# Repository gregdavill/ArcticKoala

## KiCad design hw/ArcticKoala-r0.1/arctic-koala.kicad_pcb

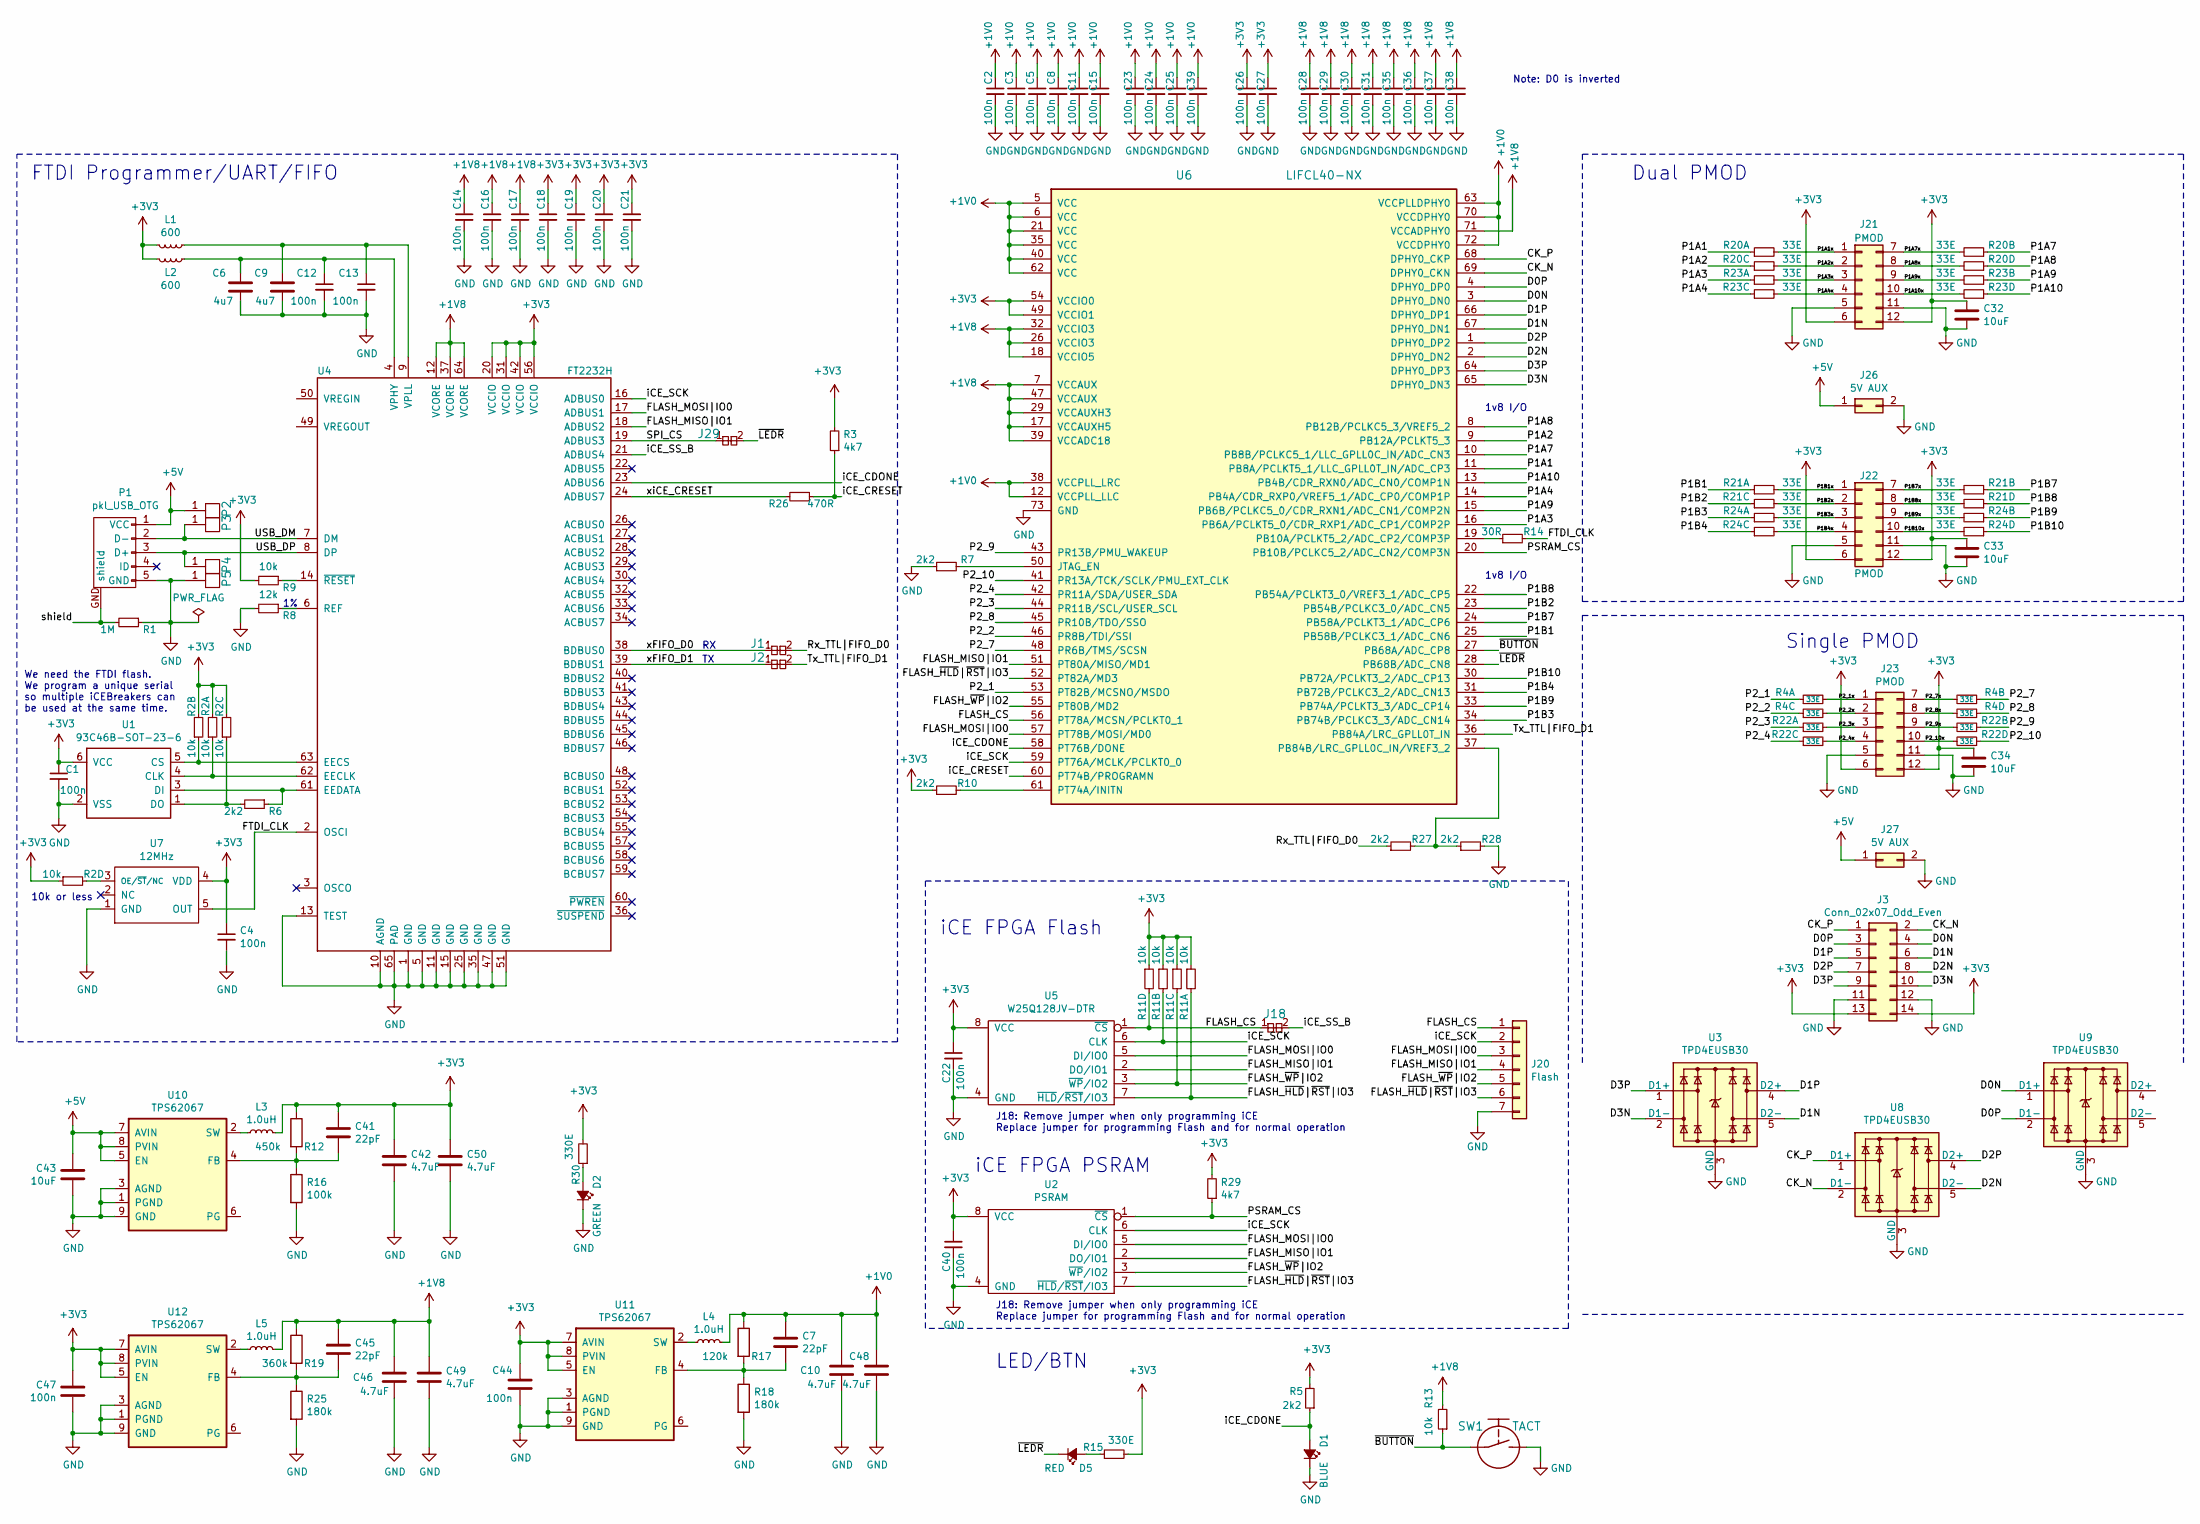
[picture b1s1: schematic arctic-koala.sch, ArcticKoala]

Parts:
C1, C2, C3, C4, C5, C8, C11, C12, C13, C14, C15, C16, C17, C18, C19, C20, C21, C22, C23, C24, C25, C26, C27, C28, C29, C30, C31, C35, C36, C37, C38, C39, C40, C44, C47: 100n; C_0402
C6, C9: 4u7; C_0603
C7, C41, C45: 22pF; C_0402
C10, C42, C46, C48, C49, C50: 4.7uF; C_0402
C32, C33, C34, C43: 10uF; C_0603
D1: BLUE; D_0603
D2: GREEN; D_0603
D5: RED; D_0603
J1, J2, J18, J29: Jumper; J_NC_0603_15
J3: Conn_02x07_Odd_Even; PinSocket_2x07_P2.54mm_Vertical
J20: Flash; Pin_Header_Straight_1x07
J21, J22, J23: PMOD; Socket_Strip_Angled_2x06
J26, J27: 5V AUX; Pin_Header_Straight_2x01
L1, L2: 600; L_0402
L3, L4, L5: 1.0uH; L_0603_1608Metric
P1: pkl_USB_OTG; Connector_USB_Micro_B_SMD
P2, P3, P4, P5: UP; PAD_SMD_1x2.65
R1: 1M; R_0402
R2, R11: 10k; R_Array_Convex_4x0402
R3, R29: 4k7; R_0402
R4, R20, R21, R22, R23, R24: 33E; R_Array_Convex_4x0402
R5, R6, R7, R10, R27, R28: 2k2; R_0402
R8: 12k; R_0402
R9, R13: 10k; R_0402
R12: 450k; R_0402
R14: 30R; R_0402
R15, R30: 330E; R_0402
R16: 100k; R_0402
R17: 120k; R_0402
R18, R25: 180k; R_0402
R19: 360k; R_0402
R26: 470R; R_0402
SW1: TACT; SW_SPST_3x4x2.5
U1: 93C46B-SOT-23-6; SOT-23-6
U2: PSRAM; SOIC-8_5.3x5.3mm_Pitch1.27mm
U3, U8, U9: TPD4EUSB30; USON-10_2.5x1.0mm_P0.5mm
U4: FT2232H; QFN-64-4.45mm1EP_9x9mm_Pitch0.5mm
U5: W25Q128JV-DTR; SOIC-8_5.3x5.3mm_Pitch1.27mm
U6: LIFCL40-NX; QFN-72-1EP_10x10mm_P0.5mm_EP6x6mm
U7: 12MHz; SOT-23-5
U10, U11, U12: TPS62067; WSON-8-1EP_2x2mm_P0.5mm_EP0.9x1.6mm_ThermalVias

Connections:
+1V0: C2.1, C3.1, C5.1, C7.1, C8.1, C10.1, C11.1, C15.1, C23.1, C24.1, C25.1, C39.1, C48.1, L4.2, R17.1, U6.5 (VCC), U6.6 (VCC), U6.12 (VCCPLL_LLC), U6.21 (VCC), U6.35 (VCC), U6.38 (VCCPLL_LRC), U6.40 (VCC), U6.62 (VCC), U6.63 (VCCPLLDPHY0), U6.70 (VCCDPHY0), U6.72 (VCCDPHY0)
+1V8: C14.1, C16.1, C17.1, C28.1, C29.1, C30.1, C31.1, C35.1, C36.1, C37.1, C38.1, C45.1, C46.1, C49.1, L5.2, R13.2, R19.1, U4.12 (VCORE), U4.37 (VCORE), U4.64 (VCORE), U6.7 (VCCAUX), U6.17 (VCCAUXH5), U6.18 (VCCIO5), U6.26 (VCCIO3), U6.29 (VCCAUXH3), U6.32 (VCCIO3), U6.39 (VCCADC18), U6.47 (VCCAUX), U6.71 (VCCADPHY0)
+3V3: C1.1, C4.1, C18.1, C19.1, C20.1, C21.1, C22.1, C26.1, C27.1, C32.2, C33.2, C34.2, C40.1, C41.1, C42.1, C44.1, C47.1, C50.1, J3.13, J3.14, J21.6, J21.12, J22.6, J22.12, J23.6, J23.12, L1.1, L2.1, L3.2, R2.2, R2.4, R2.6, R2.7, R3.2, R5.2, R9.2, R10.1, R11.1, R11.3, R11.5, R11.7, R12.1, R15.2, R29.2, R30.2, U1.6 (VCC), U2.8 (VCC), U4.20 (VCCIO), U4.31 (VCCIO), U4.42 (VCCIO), U4.56 (VCCIO), U5.8 (VCC), U6.49 (VCCIO1), U6.54 (VCCIO0), U7.4 (VDD), U11.5 (EN), U11.7 (AVIN), U11.8 (PVIN), U12.5 (EN), U12.7 (AVIN), U12.8 (PVIN)
+5V: C43.1, J26.1, J27.1, P1.1 (VCC), P2.1, U10.5 (EN), U10.7 (AVIN), U10.8 (PVIN)
/CK_N: J3.2, U6.69 (DPHY0_CKN), U8.2 (D1-)
/CK_P: J3.1, U6.68 (DPHY0_CKP), U8.1 (D1+)
/D0N: J3.4, U6.3 (DPHY0_DN0), U9.1 (D1+)
/D0P: J3.3, U6.4 (DPHY0_DP0), U9.2 (D1-)
/D1N: J3.6, U3.5 (D2-), U6.67 (DPHY0_DN1)
/D1P: J3.5, U3.4 (D2+), U6.66 (DPHY0_DP1)
/D2N: J3.8, U6.2 (DPHY0_DN2), U8.5 (D2-)
/D2P: J3.7, U6.1 (DPHY0_DP2), U8.4 (D2+)
/D3N: J3.10, U3.2 (D1-), U6.65 (DPHY0_DN3)
/D3P: J3.9, U3.1 (D1+), U6.64 (DPHY0_DP3)
/FLASH_CS: J18.1, J20.1, R11.8, U5.1 (~CS), U6.56 (PT78A/MCSN/PCLKT0_1)
/FLASH_MISO|IO1: J20.4, U2.2 (DO/IO1), U4.18 (ADBUS2), U5.2 (DO/IO1), U6.51 (PT80A/MISO/MD1)
/FLASH_MOSI|IO0: J20.3, U2.5 (DI/IO0), U4.17 (ADBUS1), U5.5 (DI/IO0), U6.57 (PT78B/MOSI/MD0)
/FLASH_~HLD~|~RST~|IO3: J20.6, R11.2, U2.7 (~HLD~/~RST~/IO3), U5.7 (~HLD~/~RST~/IO3), U6.52 (PT82A/MD3)
/FLASH_~WP~|IO2: J20.5, R11.6, U2.3 (~WP~/IO2), U5.3 (~WP~/IO2), U6.55 (PT80B/MD2)
/FTDI_CLK: R14.2, U4.2 (OSCI), U7.5 (OUT)
/P1A1: R20.1, U6.11 (PB8A/PCLKT5_1/LLC_GPLL0T_IN/ADC_CP3)
/P1A1x: J21.1, R20.2
/P1A2: R20.5, U6.9 (PB12A/PCLKT5_3)
/P1A2x: J21.2, R20.6
/P1A3: R23.1, U6.16 (PB6A/PCLKT5_0/CDR_RXP1/ADC_CP1/COMP2P)
/P1A3x: J21.3, R23.2
/P1A4: R23.5, U6.14 (PB4A/CDR_RXP0/VREF5_1/ADC_CP0/COMP1P)
/P1A4x: J21.4, R23.6
/P1A7: R20.3, U6.10 (PB8B/PCLKC5_1/LLC_GPLL0C_IN/ADC_CN3)
/P1A7x: J21.7, R20.4
/P1A8: R20.7, U6.8 (PB12B/PCLKC5_3/VREF5_2)
/P1A8x: J21.8, R20.8
/P1A9: R23.3, U6.15 (PB6B/PCLKC5_0/CDR_RXN1/ADC_CN1/COMP2N)
/P1A9x: J21.9, R23.4
/P1A10: R23.7, U6.13 (PB4B/CDR_RXN0/ADC_CN0/COMP1N)
/P1A10x: J21.10, R23.8
/P1B1: R21.1, U6.25 (PB58B/PCLKC3_1/ADC_CN6)
/P1B1x: J22.1, R21.2
/P1B2: R21.5, U6.23 (PB54B/PCLKC3_0/ADC_CN5)
/P1B2x: J22.2, R21.6
/P1B3: R24.1, U6.34 (PB74B/PCLKC3_3/ADC_CN14)
/P1B3x: J22.3, R24.2
/P1B4: R24.5, U6.31 (PB72B/PCLKC3_2/ADC_CN13)
/P1B4x: J22.4, R24.6
/P1B7: R21.3, U6.24 (PB58A/PCLKT3_1/ADC_CP6)
/P1B7x: J22.7, R21.4
/P1B8: R21.7, U6.22 (PB54A/PCLKT3_0/VREF3_1/ADC_CP5)
/P1B8x: J22.8, R21.8
/P1B9: R24.3, U6.33 (PB74A/PCLKT3_3/ADC_CP14)
/P1B9x: J22.9, R24.4
/P1B10: R24.7, U6.30 (PB72A/PCLKT3_2/ADC_CP13)
/P1B10x: J22.10, R24.8
/P2_1: R4.1, U6.53 (PT82B/MCSNO/MSDO)
/P2_1x: J23.1, R4.2
/P2_2: R4.5, U6.46 (PR8B/TDI/SSI)
/P2_2x: J23.2, R4.6
/P2_3: R22.1, U6.44 (PR11B/SCL/USER_SCL)
/P2_3x: J23.3, R22.2
/P2_4: R22.5, U6.42 (PR11A/SDA/USER_SDA)
/P2_4x: J23.4, R22.6
/P2_7: R4.3, U6.48 (PR6B/TMS/SCSN)
/P2_7x: J23.7, R4.4
/P2_8: R4.7, U6.45 (PR10B/TDO/SSO)
/P2_8x: J23.8, R4.8
/P2_9: R22.3, U6.43 (PR13B/PMU_WAKEUP)
/P2_9x: J23.9, R22.4
/P2_10: R22.7, U6.41 (PR13A/TCK/SCLK/PMU_EXT_CLK)
/P2_10x: J23.10, R22.8
/PSRAM_CS: R29.1, U2.1 (~CS), U6.20 (PB10B/PCLKC5_2/ADC_CN2/COMP3N)
/Rx_TTL|FIFO_D0: J1.2, R27.1
/SPI_CS: J29.1, U4.19 (ADBUS3)
/Tx_TTL|FIFO_D1: J2.2, U6.36 (PB84A/LRC_GPLL0T_IN)
/USB_DM: P1.2 (D-), P3.1, U4.7 (DM)
/USB_DP: P1.3 (D+), P4.1, U4.8 (DP)
/iCE_CDONE: D1.A, R5.1, U4.23 (ADBUS6), U6.58 (PT76B/DONE)
/iCE_CRESET: R3.1, R26.1, U6.60 (PT74B/PROGRAMN); also elsewhere on the board
/iCE_SCK: J20.2, R11.4, U2.6 (CLK), U4.16 (ADBUS0), U5.6 (CLK), U6.59 (PT76A/MCLK/PCLKT0_0)
/iCE_SS_B: J18.2, U4.21 (ADBUS4)
/shield: P1.GND (shield), R1.2
/xFIFO_D0: J1.1, U4.38 (BDBUS0)
/xFIFO_D1: J2.1, U4.39 (BDBUS1)
/xiCE_CRESET: R26.2, U4.24 (ADBUS7)
/~BUTTON: R13.1, SW1.1, U6.27 (PB68A/ADC_CP8)
/~LEDR: D5.C, J29.2, U6.28 (PB68B/ADC_CN8)
GND: C1.2, C2.2, C3.2, C4.2, C5.2, C6.2, C8.2, C9.2, C10.2, C11.2, C12.2, C13.2, C14.2, C15.2, C16.2, C17.2, C18.2, C19.2, C20.2, C21.2, C22.2, C23.2, C24.2, C25.2, C26.2, C27.2, C28.2, C29.2, C30.2, C31.2, C32.1, C33.1, C34.1, C35.2, C36.2, C37.2, C38.2, C39.2, C40.2, C42.2, C43.2, C44.2, C46.2, C47.2, C48.2, C49.2, C50.2, D1.C, D2.C, J3.11, J3.12, J20.7, J21.5, J21.11, J22.5, J22.11, J23.5, J23.11, J26.2, J27.2, P1.5 (GND), P5.1, R1.1, R7.1, R8.2, R16.2, R18.2, R25.2, R28.2, SW1.2, U1.2 (VSS), U2.4 (GND), U3.3 (GND), U3.8 (GND), U4.1 (GND), U4.5 (GND), U4.10 (AGND), U4.11 (GND), U4.13 (TEST), U4.15 (GND), U4.25 (GND), U4.35 (GND), U4.47 (GND), U4.51 (GND), U4.65 (PAD), U5.4 (GND), U6.73 (GND), U7.1 (GND), U8.3 (GND), U8.8 (GND), U9.3 (GND), U9.8 (GND), U10.1 (PGND), U10.3 (AGND), U10.9 (GND), U11.1 (PGND), U11.3 (AGND), U11.9 (GND), U12.1 (PGND), U12.3 (AGND), U12.9 (GND); also elsewhere on the board
unnamed: C7.2, R17.2, R18.1, U11.4 (FB)
unnamed: C6.1, C12.1, L2.2, U4.4 (VPHY)
unnamed: C9.1, C13.1, L1.2, U4.9 (VPLL)
unnamed: C41.2, R12.2, R16.1, U10.4 (FB)
unnamed: C45.2, R19.2, R25.1, U12.4 (FB)
unnamed: D2.A, R30.1
unnamed: D5.A, R15.1
unnamed: L3.1, U10.2 (SW)
unnamed: L4.1, U11.2 (SW)
unnamed: L5.1, U12.2 (SW)
unnamed: R2.1, U1.4 (CLK), U4.62 (EECLK)
unnamed: R2.3, U1.5 (CS), U4.63 (EECS)
unnamed: R2.5, R6.2, U1.1 (DO)
unnamed: R2.8, U7.3 (OE/~ST~/NC)
unnamed: R6.1, U1.3 (DI), U4.61 (EEDATA)
unnamed: R7.2, U6.50 (JTAG_EN)
unnamed: R8.1, U4.6 (REF)
unnamed: R9.1, U4.14 (~RESET)
unnamed: R10.2, U6.61 (PT74A/INITN)
unnamed: R14.1, U6.19 (PB10A/PCLKT5_2/ADC_CP2/COMP3P)
unnamed: R27.2, R28.1, U6.37 (PB84B/LRC_GPLL0C_IN/VREF3_2)

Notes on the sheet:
10k or less
FTDI Programmer/UART/FIFO
J18: Remove jumper when only programming iCE Replace jumper for programming Flash and for normal operation
iCE FPGA Flash
Dual PMOD
Single PMOD
LED/BTN
We need the FTDI flash. We program a unique serial so multiple iCEBreakers can be used at the same time.
1v8 I/O
Note: D0 is inverted
iCE FPGA PSRAM

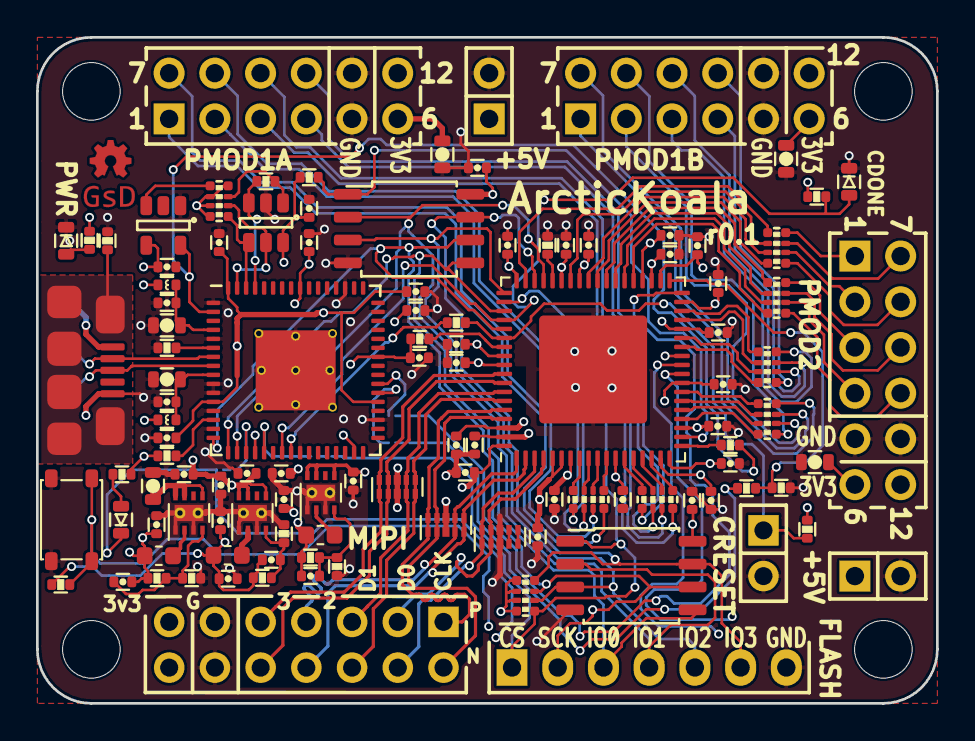
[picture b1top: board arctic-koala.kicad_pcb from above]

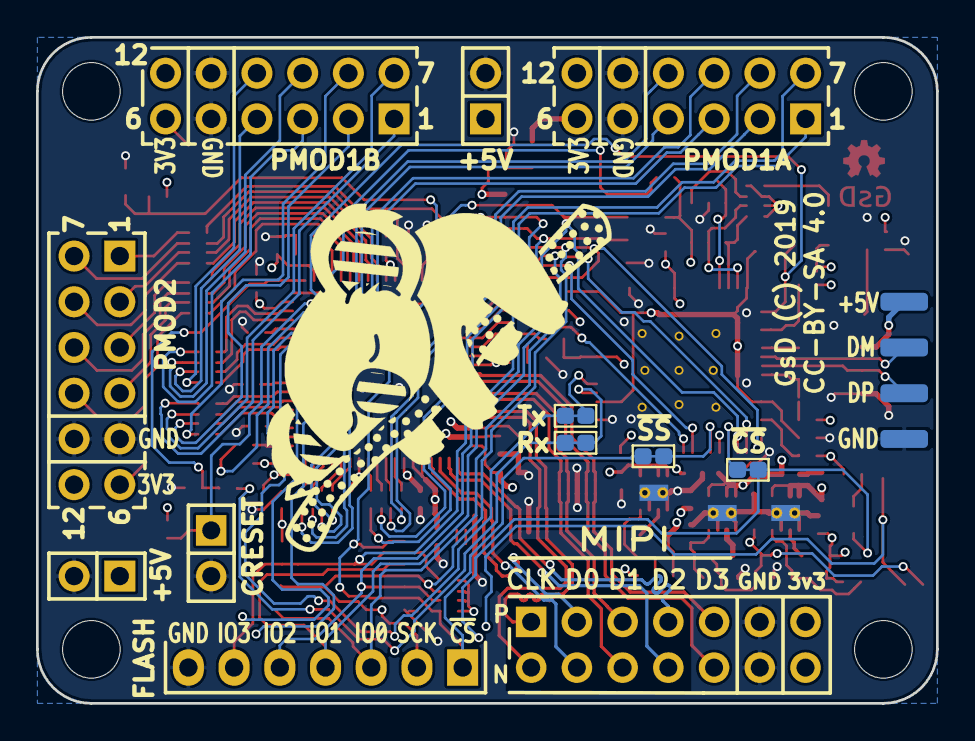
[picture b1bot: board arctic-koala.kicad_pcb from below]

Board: 4 copper layers, 50.0 x 37.0 mm, 118 parts (9 on the bottom side), 106 nets.

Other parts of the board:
J28: CRESET; PinHeader_2x01_P2.54mm_Vertical

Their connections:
/iCE_CRESET: J28.1; also elsewhere on the board
GND: J28.2; also elsewhere on the board

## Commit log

2019-12-14 Updated submodules
2019-12-14 Updated KiCad files
2019-12-15 Added ESD protection to MIPI lines
2019-12-15 Completed hardware design files
2019-12-15 Added logo to PCB, cleaned up Silkscreen
2020-10-22 hw: Add Gerbers, BOM

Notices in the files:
hw/ArcticKoala-r0.1/arctic-koala.kicad_pcb:
(C) 2019 Greg Davill
License: CC-BY-SA 4.0
GsD (C) 2019
CC-BY-SA 4.0
hw/ArcticKoala-r0.1/arctic-koala.sch:
License: CC-BY-SA V4.0
